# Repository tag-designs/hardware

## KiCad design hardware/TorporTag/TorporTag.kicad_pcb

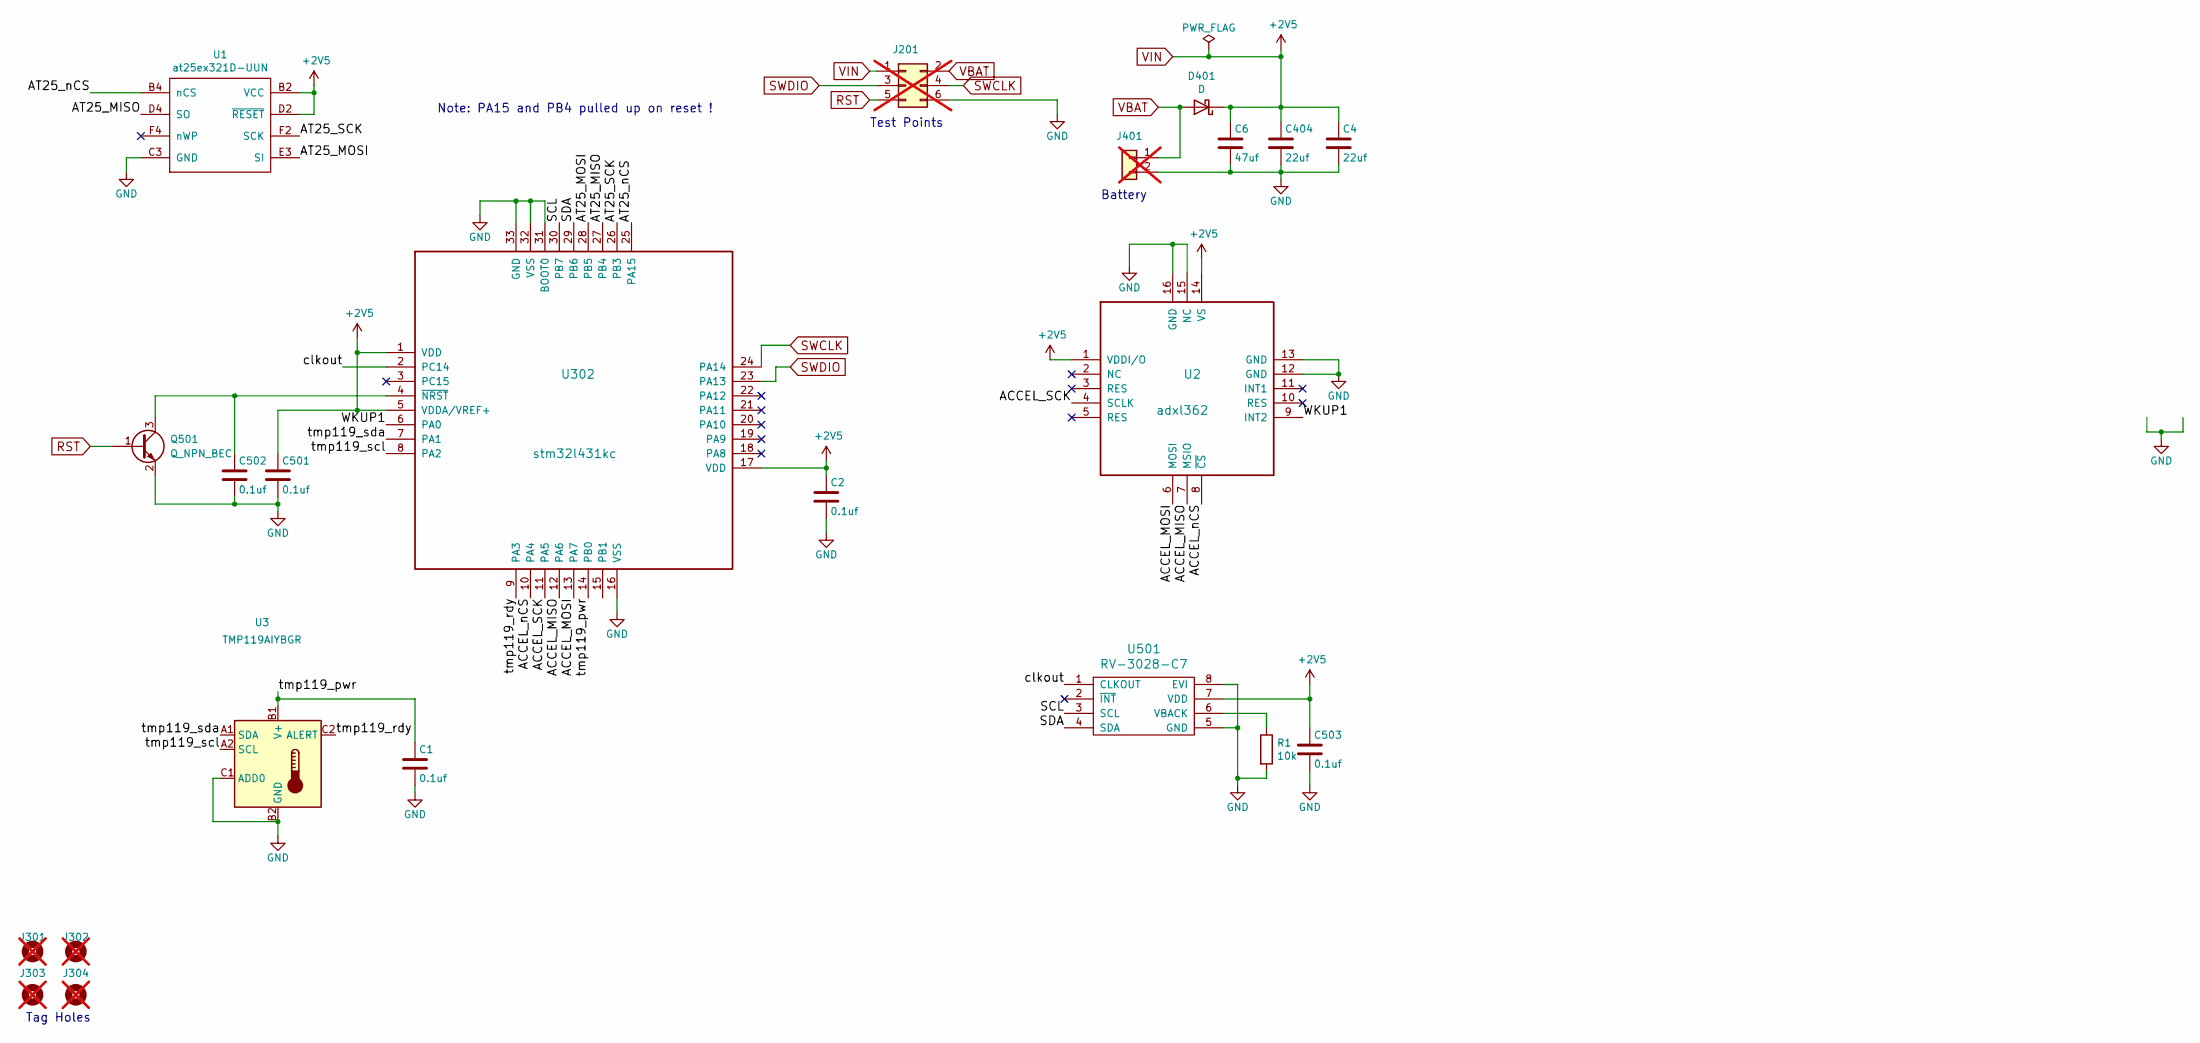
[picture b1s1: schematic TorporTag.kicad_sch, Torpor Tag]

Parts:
C1, C2, C501, C502, C503: 0.1uf; C_0201_0603Metric; MPN GRM033R60J104KE19D; LCSC C76928
C4, C404: 22uf; C_0402_1005Metric; MPN 04026D226MAT2A; LCSC C2179118
C6: 47uf; C_0603_1608Metric; MPN GRM188R60J476ME15D; LCSC C140782
D401: D; D_0402_1005Metric; MPN CDBQC0130L-HF; LCSC C2886012
J201: CONN_02X04; tagpoints6; not fitted
J301, J302, J303, J304: Conn_01x01; taghole1.1mm; not fitted
J401: CONN_01X02; MS621; not fitted
Q501: Q_NPN_BEC; SOT-883; MPN PMBT2222AMBYL; LCSC C552701
R1: 10k; R_0201_0603Metric; MPN RC0201FR-0710KL; LCSC C106225
U1: at25ex321D-UUN; adesto_wlcsp12; MPN AT25XE321D-UUN-T; LCSC C1858339
U2: adxl362; ADXL362; MPN ADXL362BCCZ-RL7; LCSC C192252
U3: TMP119AIYBGR; Texas_DSBGA-6_0.95x1.488mm_Layout2x3_P0.4mm; MPN TMP119AIYBGR; LCSC C22428347
U302: stm32l431kc; QFN-32-1EP_5x5mm_P0.5mm_EP3.45x3.45mm; MPN STM32L432KCU6; LCSC C1337280
U501: RV-3028-C7; RV-8803-C7; MPN RV-3028-C7 32.768KHZ 1PPM-TA-QA; LCSC C3019759

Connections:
/ACCEL_MISO: U2.7 (MSIO), U302.12 (PA6)
/ACCEL_MOSI: U2.6 (MOSI), U302.13 (PA7)
/ACCEL_SCK: U2.4 (SCLK), U302.11 (PA5)
/ACCEL_nCS: U2.8 (~CS), U302.10 (PA4)
/AT25_MISO: U1.D4 (SO), U302.27 (PB4)
/AT25_MOSI: U1.E3 (SI), U302.28 (PB5)
/AT25_SCK: U1.F2 (SCK), U302.26 (PB3)
/AT25_nCS: U1.B4 (nCS), U302.25 (PA15)
/SCL: U302.30 (PB7), U501.3 (SCL)
/SDA: U302.29 (PB6), U501.4 (SDA)
/WKUP1: U2.9 (INT2), U302.6 (PA0)
/clkout: U302.2 (PC14), U501.1 (CLKOUT)
/tmp119_pwr: C1.1, U3.B1 (V+), U302.14 (PB0)
/tmp119_rdy: U3.C2 (ALERT), U302.9 (PA3)
/tmp119_scl: U3.A2 (SCL), U302.8 (PA2)
/tmp119_sda: U3.A1 (SDA), U302.7 (PA1)
GND: C1.2, C2.2, C4.2, C6.2, C404.2, C501.2, C502.2, C503.2, J201.6, J401.2, Q501.2 (E), R1.2, U1.C3 (GND), U2.12 (GND), U2.13 (GND), U2.15 (NC), U2.16 (GND), U3.B2 (GND), U3.C1 (ADD0), U302.16 (VSS), U302.31 (BOOT0), U302.32 (VSS), U302.33 (GND), U501.5 (GND), U501.8 (EVI)
unnamed: C502.1, Q501.3 (C), U302.4 (~NRST)
unnamed: R1.1, U501.6 (VBACK)
RST: J201.5, Q501.1 (B)
SWCLK: J201.4, U302.24 (PA14)
SWDIO: J201.3, U302.23 (PA13)
VBAT: D401.2 (A), J201.2, J401.1
VIN: C2.1, C4.1, C6.1, C404.1, C501.1, C503.1, D401.1 (K), J201.1, U1.B2 (VCC), U1.D2 (~RESET), U2.1 (VDDI/O), U2.14 (VS), U302.1 (VDD), U302.5 (VDDA/VREF+), U302.17 (VDD), U501.7 (VDD)

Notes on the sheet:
Note: PA15 and PB4 pulled up on reset !
Tag Holes
Test Points
Battery

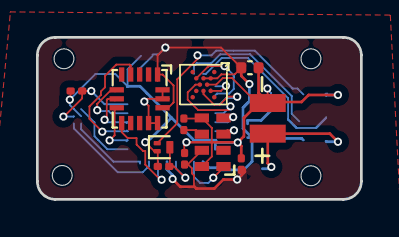
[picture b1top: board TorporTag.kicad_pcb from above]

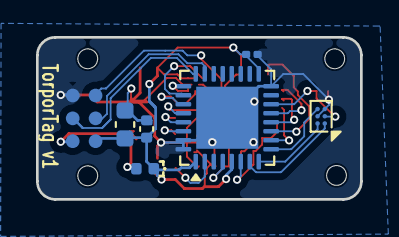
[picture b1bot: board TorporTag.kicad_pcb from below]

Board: 2 copper layers, 18.0 x 9.0 mm, 22 parts (7 on the bottom side), 24 nets.

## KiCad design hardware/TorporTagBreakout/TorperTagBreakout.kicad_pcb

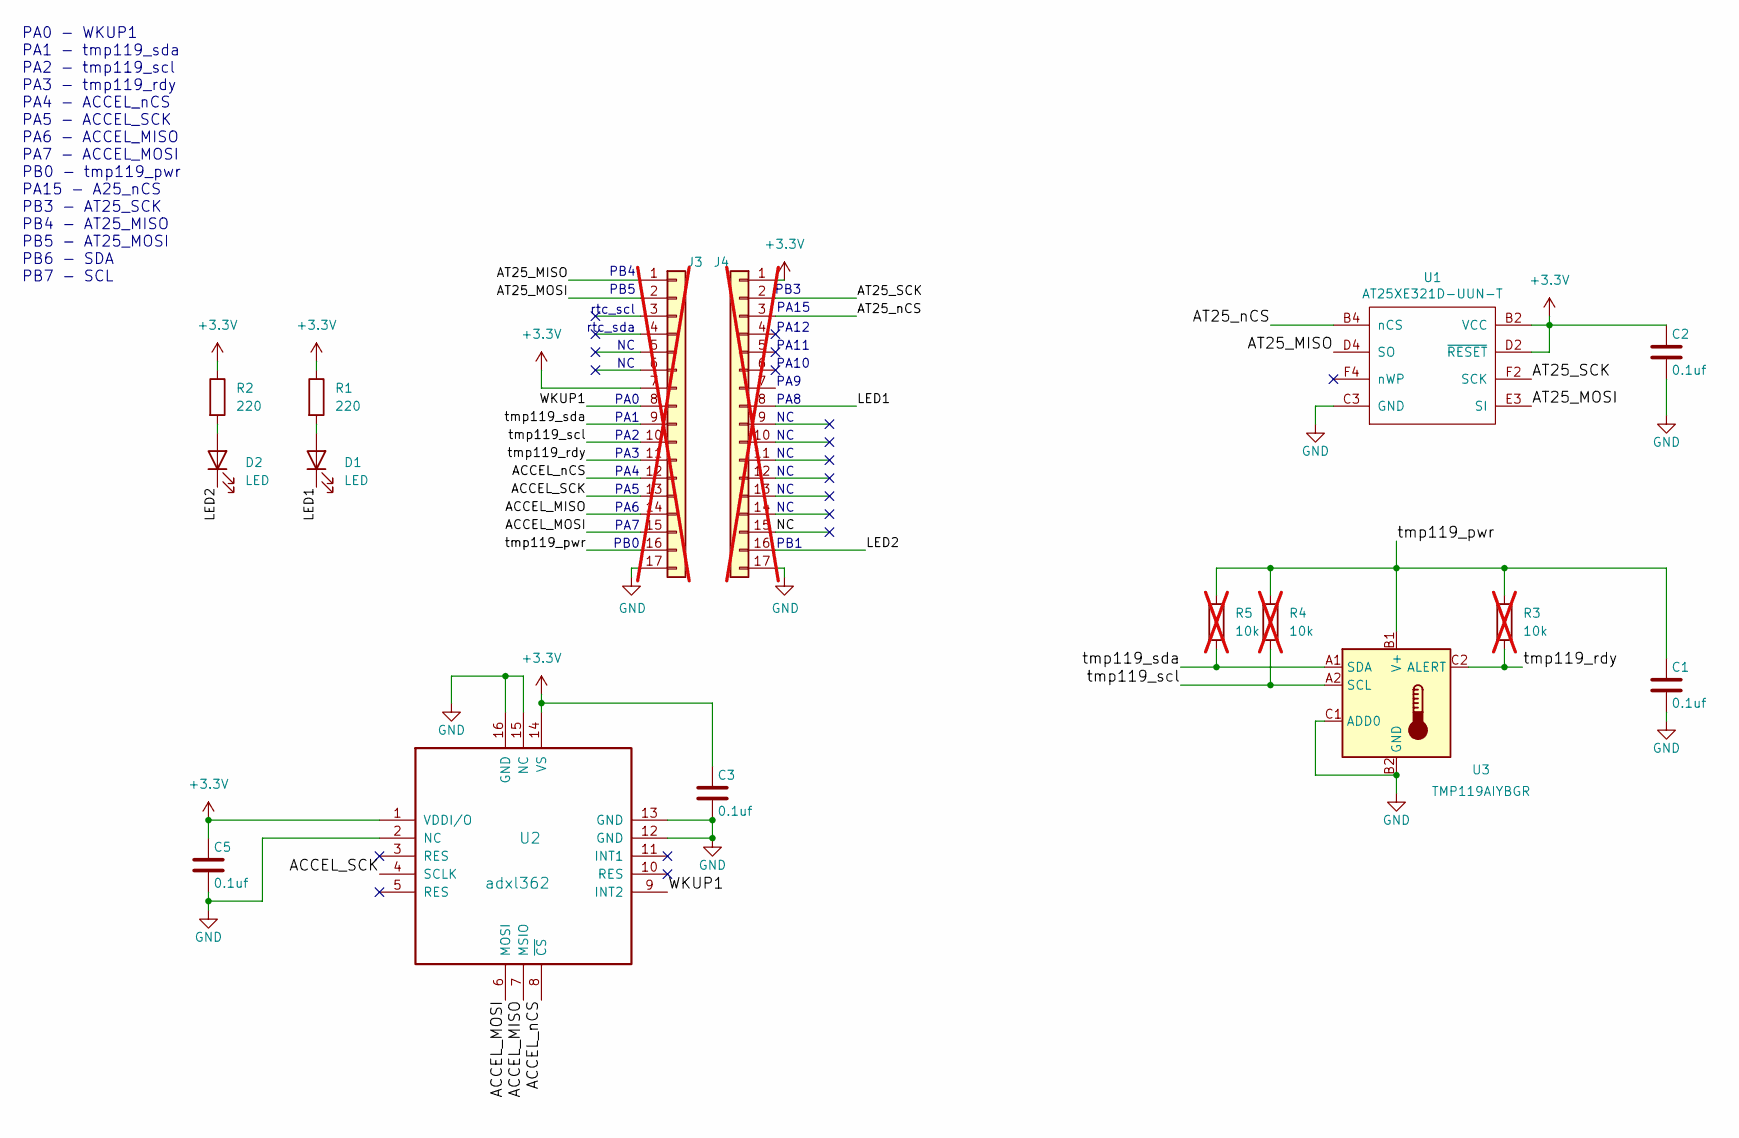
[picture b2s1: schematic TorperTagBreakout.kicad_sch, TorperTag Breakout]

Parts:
C1, C2, C3, C5: 0.1uf; C_0603_1608Metric; MPN CC0603KRX7R9BB104; LCSC C14663
D1, D2: LED; LED_0603_1608Metric; MPN KT-0603R; LCSC C2286
J3, J4: Conn_01x17; PinHeader_1x17_P2.54mm_Vertical_Staggered; not fitted
R1, R2: 220; R_0603_1608Metric; MPN 0603WAF2200T5E; LCSC C22962
R3, R4, R5: 10k; R_0805_2012Metric; MPN 0805W8F1002T5E; LCSC C17414; not fitted
U1: AT25XE321D-UUN-T; adesto_wlcsp12; MPN AT25XE321D-UUN-T; LCSC C1852767
U2: adxl362; ADXL362; MPN ADXL362BCCZ-RL; LCSC C59641
U3: TMP119AIYBGR; Texas_DSBGA-6_0.95x1.488mm_Layout2x3_P0.4mm; MPN TMP119AIYBGR; LCSC C22428347

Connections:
+3.3V: C2.1, C3.1, C5.1, J3.7, J4.1, R1.1, R2.1, U1.B2 (VCC), U1.D2 (~RESET), U2.1 (VDDI/O), U2.14 (VS)
/ACCEL_MISO: J3.14, U2.7 (MSIO)
/ACCEL_MOSI: J3.15, U2.6 (MOSI)
/ACCEL_SCK: J3.13, U2.4 (SCLK)
/ACCEL_nCS: J3.12, U2.8 (~CS)
/AT25_MISO: J3.1, U1.D4 (SO)
/AT25_MOSI: J3.2, U1.E3 (SI)
/AT25_SCK: J4.2, U1.F2 (SCK)
/AT25_nCS: J4.3, U1.B4 (nCS)
/LED1: D1.1 (K), J4.8
/LED2: D2.1 (K), J4.16
/NC: J4.15
/WKUP1: J3.8, U2.9 (INT2)
/tmp119_pwr: C1.1, J3.16, R3.1, R4.1, R5.1, U3.B1 (V+)
/tmp119_rdy: J3.11, R3.2, U3.C2 (ALERT)
/tmp119_scl: J3.10, R4.2, U3.A2 (SCL)
/tmp119_sda: J3.9, R5.2, U3.A1 (SDA)
GND: C1.2, C2.2, C3.2, C5.2, J3.17, J4.17, U1.C3 (GND), U2.2 (NC), U2.12 (GND), U2.13 (GND), U2.15 (NC), U2.16 (GND), U3.B2 (GND), U3.C1 (ADD0)
unnamed: D1.2 (A), R1.2
unnamed: D2.2 (A), R2.2

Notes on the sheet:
PA1
PA9
PA2
PA0
PA8
PA7
PA15
PA5
PA4
PB3
PA6
PA0 - WKUP1 PA1 - tmp119_sda PA2 - tmp119_scl PA3 - tmp119_rdy PA4 - ACCEL_nCS PA5 - ACCEL_SCK PA6 - ACCEL_MISO PA7 - ACCEL_MOSI PB0 - tmp119_pwr PA15 - A25_nCS PB3 - AT25_SCK PB4 - AT25_MISO PB5 - AT25_MOSI PB6 - SDA PB7 - SCL
PA3
PB4
PA12
PB0
PB5
PA10
rtc_sda
PA11
PB1
rtc_scl

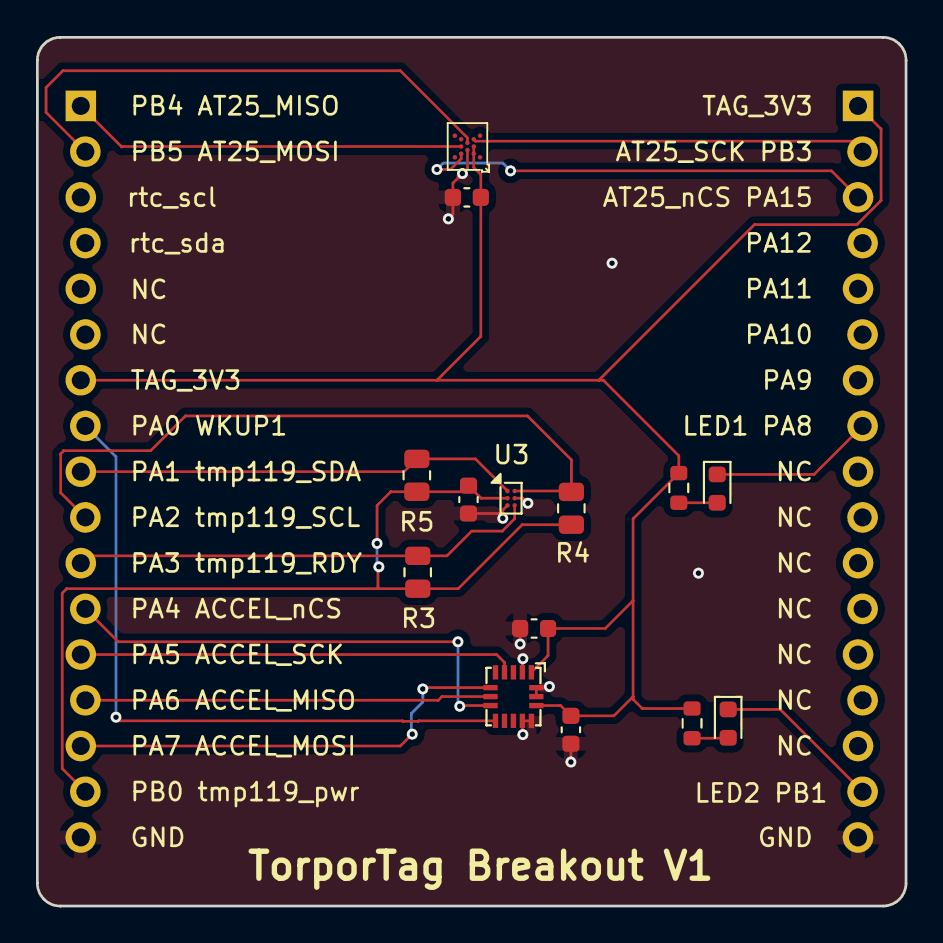
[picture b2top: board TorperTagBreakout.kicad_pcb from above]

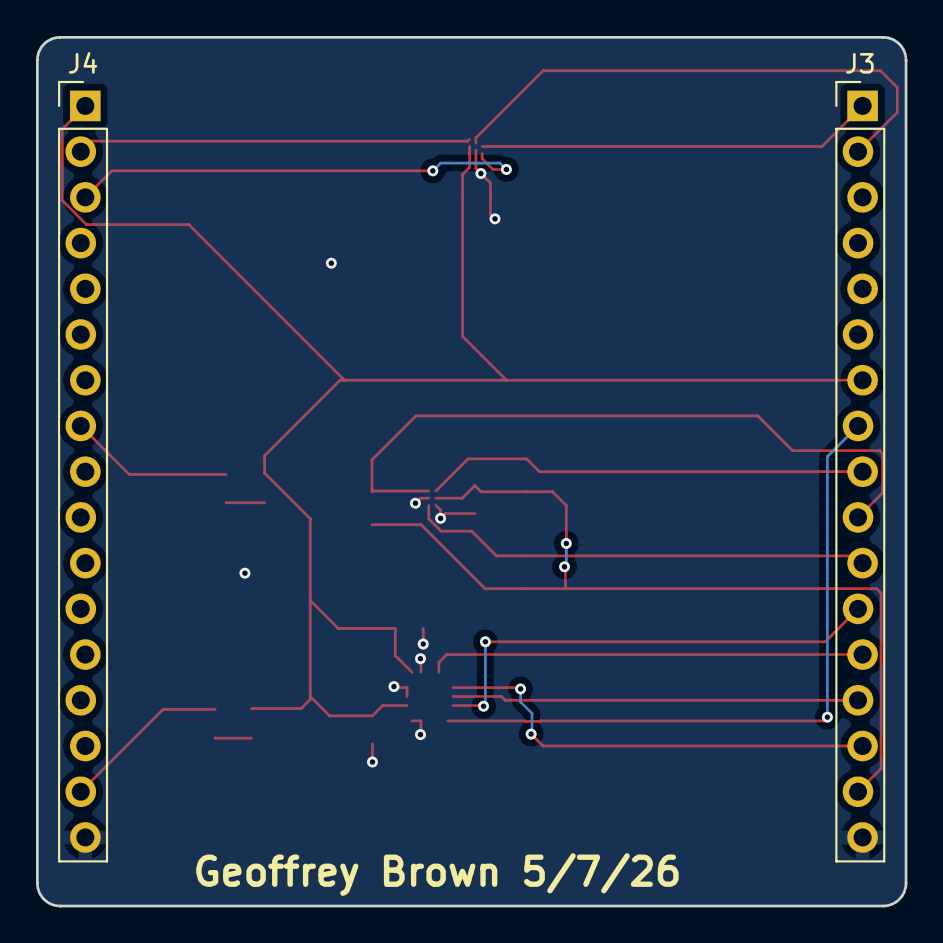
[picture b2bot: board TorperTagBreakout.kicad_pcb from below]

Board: 2 copper layers, 48.3 x 48.3 mm, 16 parts (2 on the bottom side), 19 nets.

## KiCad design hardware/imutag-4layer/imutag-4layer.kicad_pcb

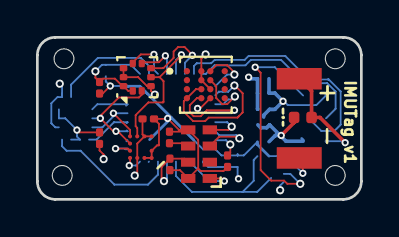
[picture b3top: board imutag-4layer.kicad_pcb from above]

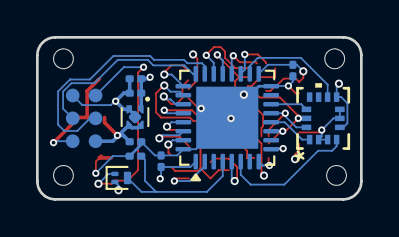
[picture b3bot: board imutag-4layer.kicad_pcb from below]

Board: 4 copper layers, 18.0 x 9.0 mm, 27 parts (11 on the bottom side), 29 nets.

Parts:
C1, C2, C3, C5, C9, C501, C502, C503: 0.1uf; C_0201_0603Metric
C4: 4.7uf; C_0201_0603Metric
C7, C8: 1uf; C_0201_0603Metric
D401: D; D_0402_1005Metric
J201: CONN_02X04; tagpoints6
J301, J302, J303, J304: Conn_01x01; taghole1.1mm
J401: CONN_01X02; batterypads
Q501: Q_NPN_BEC; SOT-883
R1: 10k; R_0201_0603Metric
U2: AK09940A; AK09940a
U3: LPS22DF; ST_HLGA-10_2x2mm_P0.5mm_LayoutBorder3x2y
U4: TPS7A2018PDQN; Texas_X2SON-4_1x1mm_P0.65mm
U5: LSM6DSV; LGA14-L_2P59X3P1X0P5_STM
U6: IC_MX25U12843GBBI00
U302: stm32l431kc; QFN-32-1EP_5x5mm_P0.5mm_EP3.45x3.45mm
U501: RV-3028-C7; RV-8803-C7

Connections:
+1V8: C1.1, C2.1, C3.1, C5.1, C8.1, C9.1, C501.1, C503.1, U2.B1 (VDD), U2.C4 (VOD), U2.D4 (RSTN), U3.1 (Vdd_IO), U3.10 (VDD), U4.1 (OUT), U5.5 (VDD_IO), U5.8 (VDD), U6.A2 (VCC), U6.B2 (~RESET), U6.C3 (~WP), U302.1 (VDD), U302.5 (VDDA/VREF+), U302.17 (VDD), U501.7 (VDD)
/AK_CS: U2.A2 (CSB), U302.9 (PA3)
/AK_TRG: U2.A1 (DRDY/TRG), U302.8 (PA2)
/AT25_MISO: U6.B3 (SO), U302.27 (PB4)
/AT25_MOSI: U6.D2 (SI), U302.28 (PB5)
/AT25_SCK: U6.C2 (SCLK), U6.D1, U302.26 (PB3)
/AT25_nCS: U6.A3 (~CS), U302.25 (PA15)
/LPS_CS: U3.6 (~CS), U302.20 (PA10)
/LPS_DRDY: U3.7 (INT_DRDY), U302.19 (PA9)
/LPS_MISO: U2.B4 (SO), U3.4 (SDA), U302.21 (PA11)
/LPS_MOSI: U3.5 (SA0), U302.22 (PA12)
/LSM_CK: U2.A3 (SCL/SK), U3.2 (SCL), U5.13 (SCL), U302.11 (PA5)
/LSM_CS: U5.12 (CS), U302.14 (PB0)
/LSM_MISO: U5.1 (SDO/SA0), U302.12 (PA6)
/LSM_MOSI: U2.A4 (SDA/SI), U5.14 (SDA), U302.13 (PA7)
/LSM_TRG: U5.9 (INT2), U302.18 (PA8)
/SCL: U302.30 (PB7), U501.3 (SCL)
/SDA: U302.29 (PB6), U501.4 (SDA)
/WKUP1: U5.4 (INT1), U302.6 (PA0)
/clkout: U302.2 (PC14), U501.1 (CLKOUT)
GND: C1.2, C2.2, C3.2, C4.1, C5.2, C7.2, C8.2, C9.2, C501.2, C502.2, C503.2, J201.6, J401.2, Q501.2 (E), R1.2, U2.C1 (VSS), U2.D1 (CAD0), U2.D2 (CAD1), U3.3 (GND), U3.8 (GND_IO), U3.9 (GND), U4.2 (GND), U4.5 (Pad), U5.2 (SDX), U5.3 (SCX), U5.6 (GND), U5.7 (GND), U6.D3 (GND), U302.16 (VSS), U302.32 (VSS), U302.33 (GND), U501.5 (GND), U501.8 (EVI)
unnamed: C502.1, Q501.3 (C), U302.4 (~NRST)
unnamed: C4.2, U302.31 (BOOT0)
unnamed: R1.1, U501.6 (VBACK)
RST: J201.5, Q501.1 (B)
SWCLK: J201.4, U302.24 (PA14)
SWDIO: J201.3, U302.23 (PA13)
VBAT: D401.2 (A), J201.2, J401.1
VIN: C7.1, D401.1 (K), J201.1, U4.3 (EN), U4.4 (IN)

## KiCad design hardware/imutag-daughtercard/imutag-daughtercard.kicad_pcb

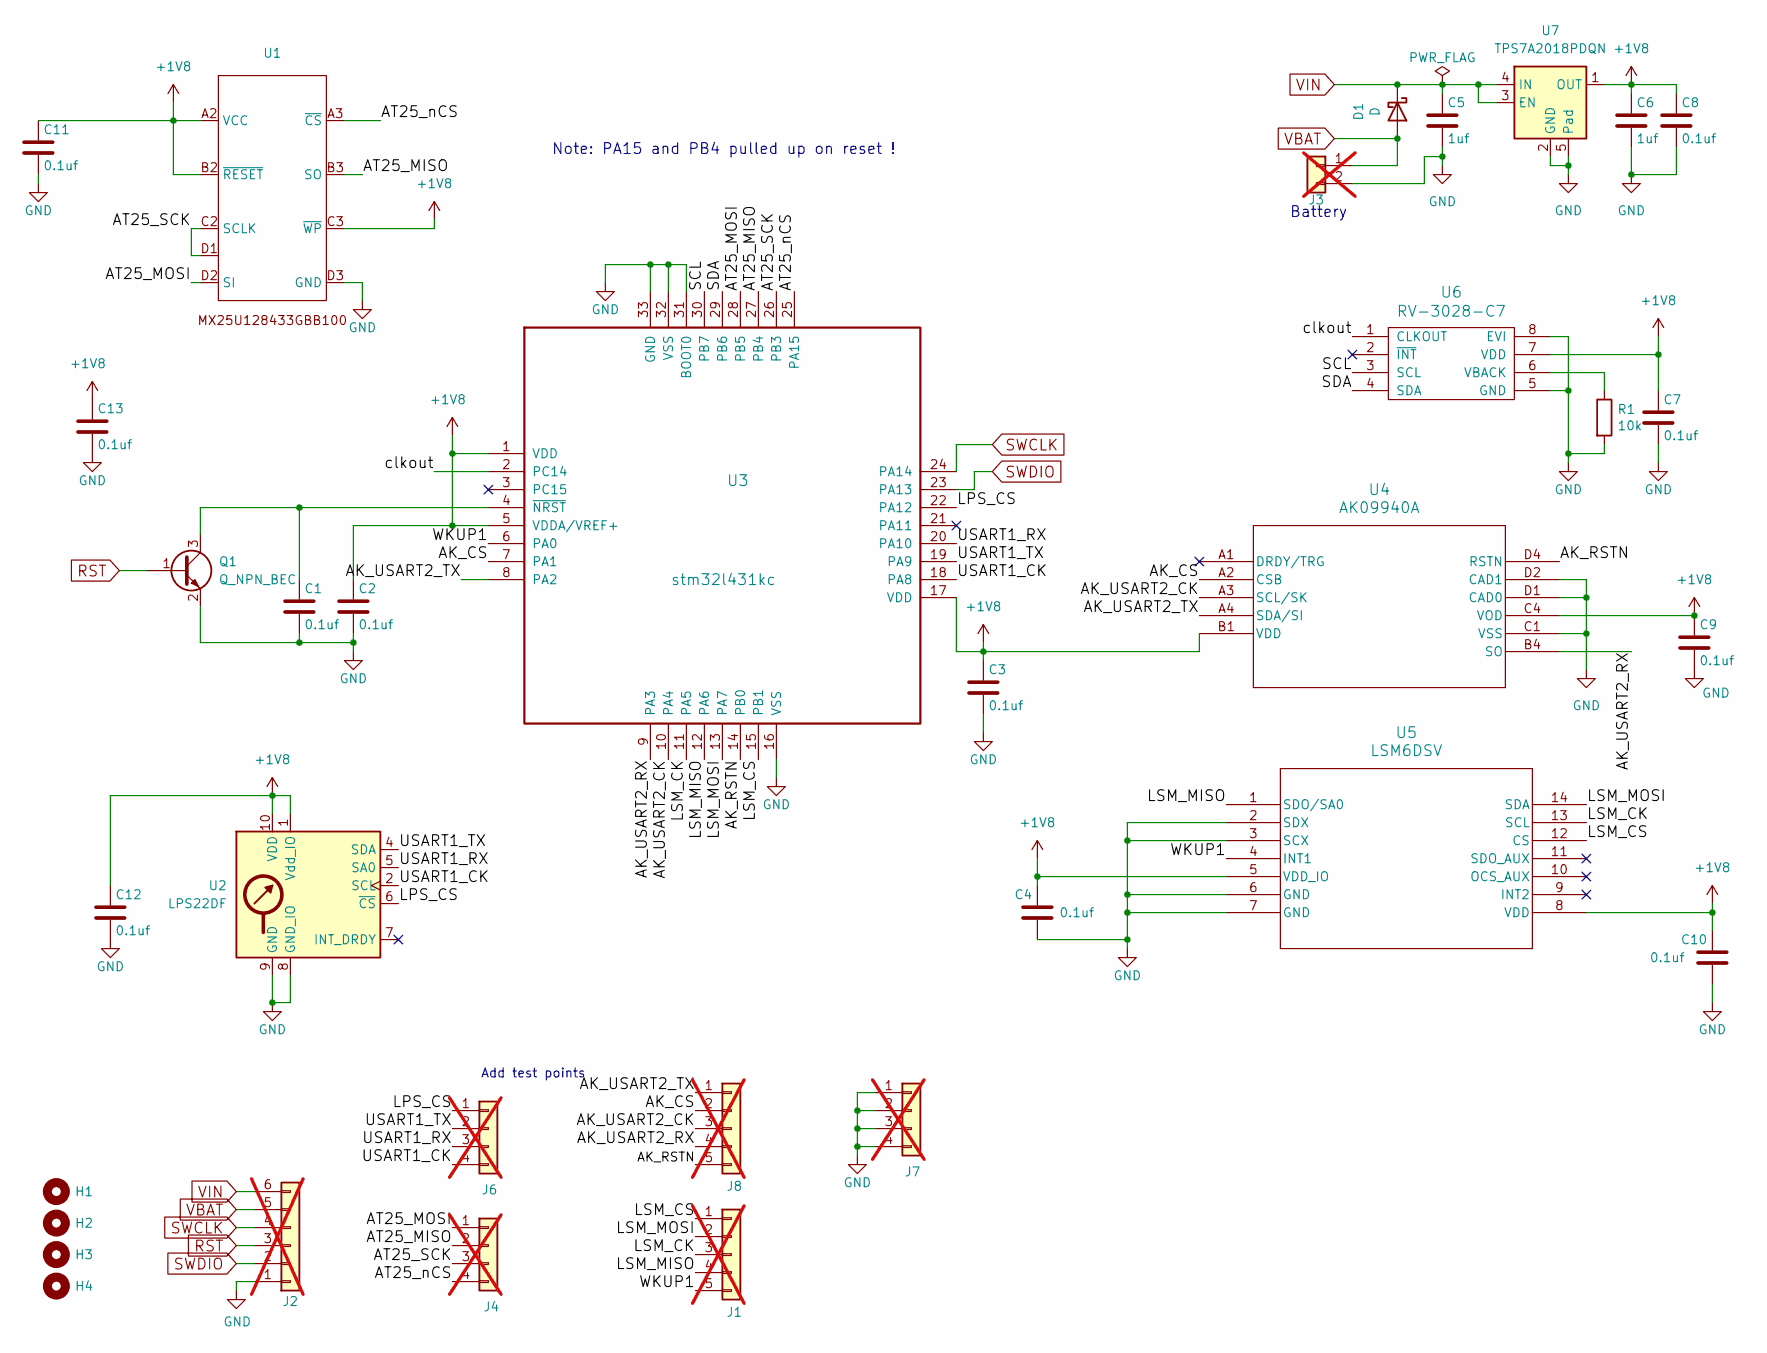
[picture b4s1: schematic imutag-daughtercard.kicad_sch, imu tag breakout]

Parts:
C1, C2, C4, C7, C10, C11, C12, C13: 0.1uf; C_0201_0603Metric; MPN C181047; LCSC C181047
C3: 0.1uf; C_0201_0603Metric; MPN GRM033R60J105MEA2D; LCSC C76929
C5, C6: 1uf; C_0201_0603Metric; MPN GRM033R60J105MEA2D
C8, C9: 0.1uf; C_0201_0603Metric; MPN GRM033C81E104KE14D
D1: D; D_0402_1005Metric; MPN CDBQC0130L-HF; LCSC C2886012
H1, H2, H3, H4: MountingHole; MountingHole_2.5mm
J1, J8: Conn_01x05; PinHeader_1x05_P2.54mm_Vertical; not fitted
J2: Conn_01x06; JST_B6B-ZR_LF__SN_; not fitted
J3: CONN_01X02; batterypads; not fitted
J4, J6, J7: Conn_01x04; PinHeader_1x04_P2.54mm_Vertical; not fitted
Q1: Q_NPN_BEC; SOT-883; MPN BC847AMB,315; LCSC C686658
R1: 10k; R_0201_0603Metric; MPN RC0201FR-0710KL; LCSC C106225
U1: IC_MX25U12843GBBI00; MPN MX25U12843GBBI00; LCSC C7316586
U2: LPS22DF; ST_HLGA-10_2x2mm_P0.5mm_LayoutBorder3x2y
U3: stm32l431kc; QFN-32-1EP_5x5mm_P0.5mm_EP3.45x3.45mm; MPN STM32L432KCU6; LCSC C1337280
U4: AK09940A; AK09940a; MPN AK09940A
U5: LSM6DSV; LGA14-L_2P59X3P1X0P5_STM
U6: RV-3028-C7; RV-8803-C7; MPN RV-3028-C7 32.768KHZ 1PPM-TA-QA; LCSC C3019759
U7: TPS7A2018PDQN; Texas_X2SON-4_1x1mm_P0.65mm; MPN TPS7A2018PDQNR

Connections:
+1V8: C2.1, C3.1, C4.1, C6.1, C7.1, C8.1, C9.1, C10.1, C11.1, C12.1, C13.1, U1.A2 (VCC), U1.B2 (~RESET), U1.C3 (~WP), U2.1 (Vdd_IO), U2.10 (VDD), U3.1 (VDD), U3.5 (VDDA/VREF+), U3.17 (VDD), U4.B1 (VDD), U4.C4 (VOD), U5.5 (VDD_IO), U5.8 (VDD), U6.7 (VDD), U7.1 (OUT)
/AK_CS: J8.2, U3.7 (PA1), U4.A2 (CSB)
/AK_RSTN: J8.5, U3.14 (PB0), U4.D4 (RSTN)
/AK_USART2_CK: J8.3, U3.10 (PA4), U4.A3 (SCL/SK)
/AK_USART2_RX: J8.4, U3.9 (PA3), U4.B4 (SO)
/AK_USART2_TX: J8.1, U3.8 (PA2), U4.A4 (SDA/SI)
/AT25_MISO: J4.2, U1.B3 (SO), U3.27 (PB4)
/AT25_MOSI: J4.1, U1.D2 (SI), U3.28 (PB5)
/AT25_SCK: J4.3, U1.C2 (SCLK), U1.D1, U3.26 (PB3)
/AT25_nCS: J4.4, U1.A3 (~CS), U3.25 (PA15)
/LPS_CS: J6.1, U2.6 (~CS), U3.22 (PA12)
/LSM_CK: J1.3, U3.11 (PA5), U5.13 (SCL)
/LSM_CS: J1.1, U3.15 (PB1), U5.12 (CS)
/LSM_MISO: J1.4, U3.12 (PA6), U5.1 (SDO/SA0)
/LSM_MOSI: J1.2, U3.13 (PA7), U5.14 (SDA)
/SCL: U3.30 (PB7), U6.3 (SCL)
/SDA: U3.29 (PB6), U6.4 (SDA)
/USART1_CK: J6.4, U2.2 (SCL), U3.18 (PA8)
/USART1_RX: J6.3, U2.5 (SA0), U3.20 (PA10)
/USART1_TX: J6.2, U2.4 (SDA), U3.19 (PA9)
/WKUP1: J1.5, U3.6 (PA0), U5.4 (INT1)
/clkout: U3.2 (PC14), U6.1 (CLKOUT)
GND: C1.2, C2.2, C3.2, C4.2, C5.2, C6.2, C7.2, C8.2, C9.2, C10.2, C11.2, C12.2, C13.2, J2.1, J3.2, J7.1, J7.2, J7.3, J7.4, Q1.2 (E), R1.2, U1.D3 (GND), U2.3 (GND), U2.8 (GND_IO), U2.9 (GND), U3.16 (VSS), U3.31 (BOOT0), U3.32 (VSS), U3.33 (GND), U4.C1 (VSS), U4.D1 (CAD0), U4.D2 (CAD1), U5.2 (SDX), U5.3 (SCX), U5.6 (GND), U5.7 (GND), U6.5 (GND), U6.8 (EVI), U7.2 (GND), U7.5 (Pad)
unnamed: C1.1, Q1.3 (C), U3.4 (~NRST)
unnamed: R1.1, U6.6 (VBACK)
RST: J2.3, Q1.1 (B)
SWCLK: J2.4, U3.24 (PA14)
SWDIO: J2.2, U3.23 (PA13)
VBAT: D1.2 (A), J2.5, J3.1
VIN: C5.1, D1.1 (K), J2.6, U7.3 (EN), U7.4 (IN)

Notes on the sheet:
Battery
Add test points
Note: PA15 and PB4 pulled up on reset !

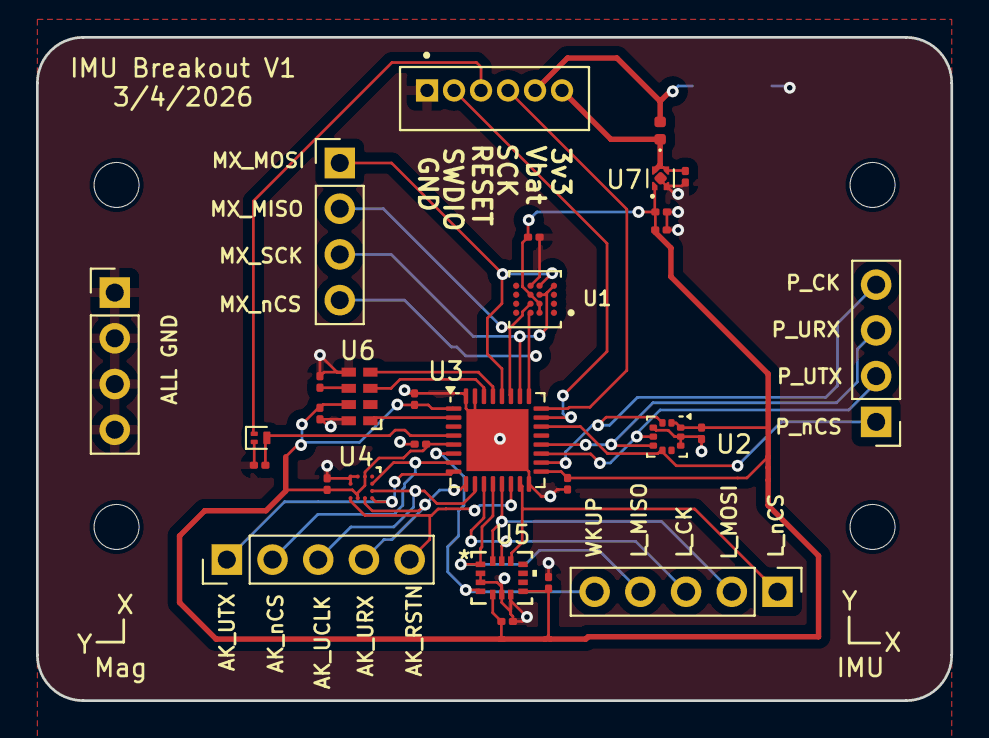
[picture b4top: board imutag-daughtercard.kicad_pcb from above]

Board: 2 copper layers, 50.8 x 36.9 mm, 34 parts (1 on the bottom side), 30 nets.

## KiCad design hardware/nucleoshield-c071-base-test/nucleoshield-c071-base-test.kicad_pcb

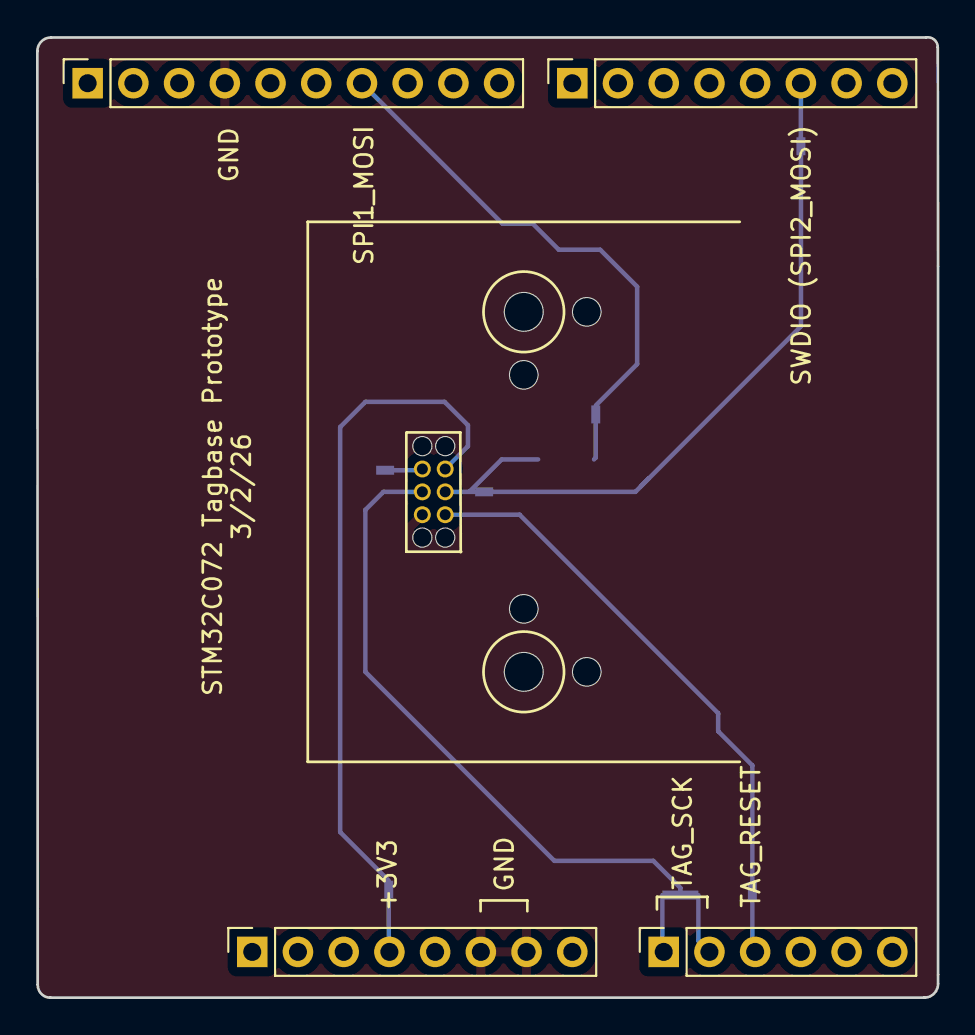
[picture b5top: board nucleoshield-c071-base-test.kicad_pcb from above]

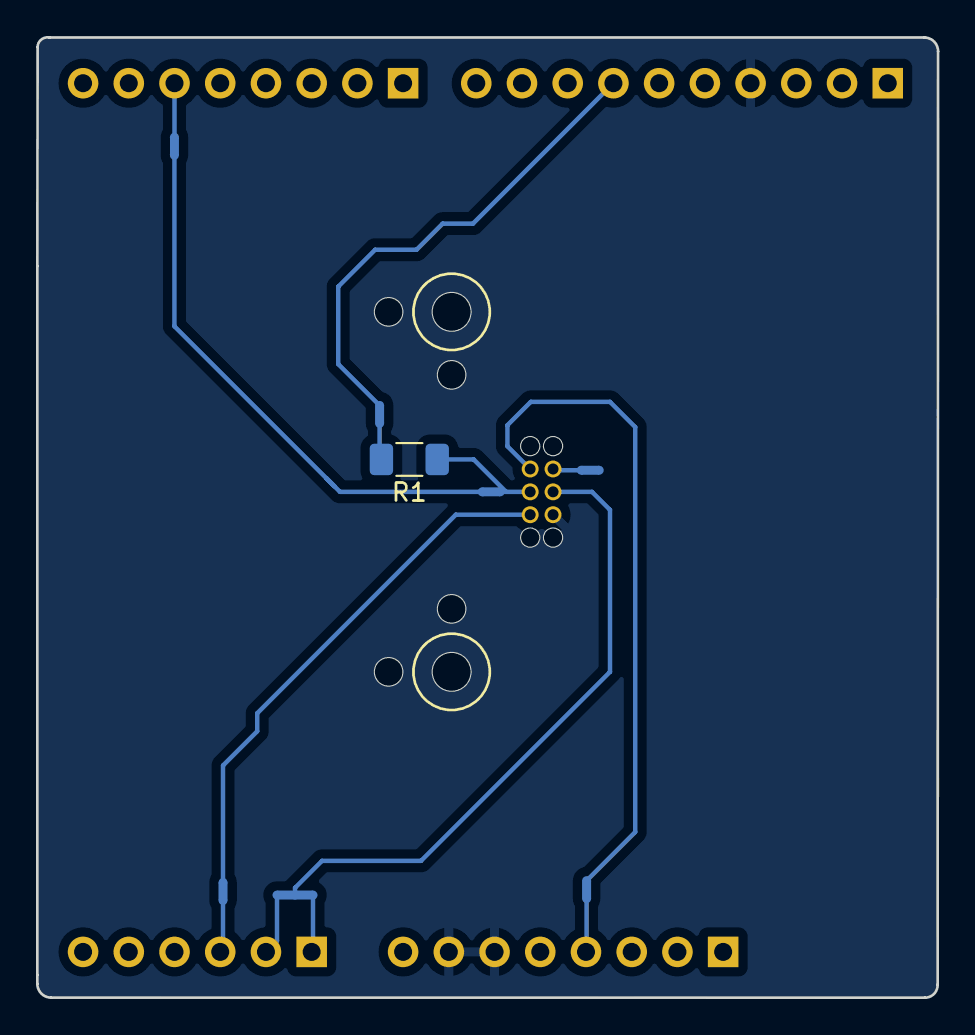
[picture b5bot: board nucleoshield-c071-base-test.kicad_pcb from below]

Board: 2 copper layers, 50.0 x 53.4 mm, 13 parts (8 on the bottom side), 14 nets.

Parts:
J1: Power; PinSocket_1x08_P2.54mm_Vertical
J2: Digital/PWM; PinSocket_1x10_P2.54mm_Vertical
J3: Analog; PinSocket_1x06_P2.54mm_Vertical
J4: Digital/PWM; PinSocket_1x08_P2.54mm_Vertical
J5: Conn_02x03_Odd_Even; 6pin_tagpoints_new_offset
NT1, NT3, NT4, NT5, NT6, NT7: NetTie_2; NetTie-2_SMD_Pad0.5mm
NT2: NetTie_3; NetTie-3_SMD_Pad0.5mm
R1: 1K; R_1206_3216Metric_Pad1.30x1.75mm_HandSolder

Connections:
+3V3: J1.4, NT7.1
/PA0: J3.1, NT2.1
/PA1: J3.2, NT2.3
/PA4: J3.3, NT6.1
/PA7: J2.7, NT3.1
/PA10: J4.6, NT4.1
/SPI1_MOSI: NT3.2, R1.2
/SPI2_MOSI: NT1.1, NT4.2
GND: J1.6, J1.7, J2.4, J5.2
TAG_3V3: J5.5, NT7.2
TAG_RESET: J5.1, NT6.2
TAG_SCK: J5.4, NT2.2
TAG_SWDIO: J5.3, NT1.2, R1.1
TAG_VBAT: J5.6, NT5.2

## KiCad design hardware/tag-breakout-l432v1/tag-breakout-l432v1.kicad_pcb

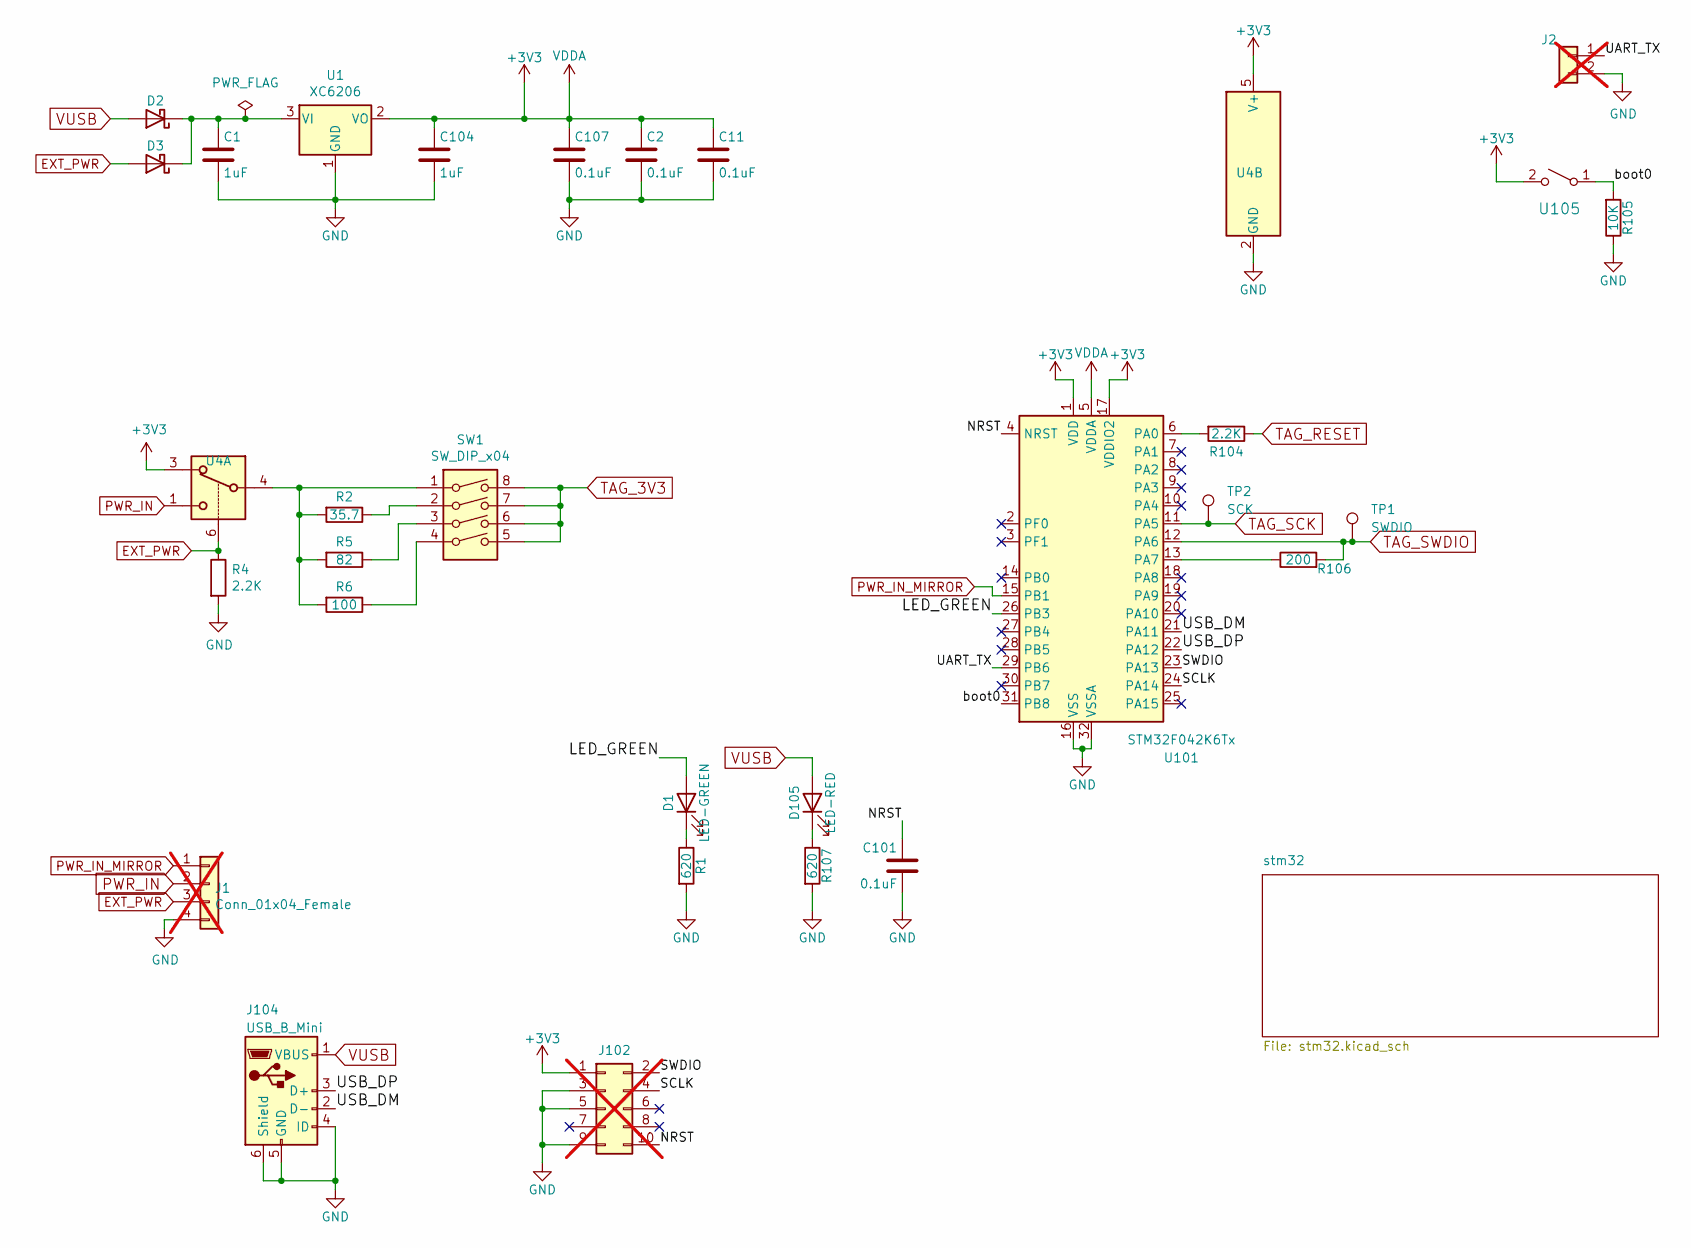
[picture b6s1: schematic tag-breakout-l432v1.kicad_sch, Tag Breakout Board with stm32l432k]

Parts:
C1, C104: 1uF; C_0603_1608Metric; MPN CL10A105KB8NNNC; LCSC C15849
C2, C11, C101, C107: 0.1uF; C_0603_1608Metric; MPN CC0603KRX7R9BB104; LCSC C14663
D1: LED-GREEN; LED_0603_1608Metric; MPN 19-217/GHC-YR1S2/3T; LCSC C72043
D2, D3: D_Schottky; D_SOD-123; LCSC C8598
D105: LED-RED; LED_0603_1608Metric; MPN KT 0603R; LCSC C2286
J1: Conn_01x04_Female; JST_XH_B04B-XH-AM_1x04_P2.50mm_Vertical; not fitted
J2: Conn_01x02_Male; PinHeader_1x02_P2.54mm_Vertical; not fitted
J102: Conn_02x05_Odd_Even; FTSH-105-01-F-D-K; not fitted
J104: USB_B_Mini; USB_Mini-B_Lumberg_2486_01_Horizontal; MPN MINI 5PTP; LCSC C2681563
R1, R107: 620; R_0603_1608Metric; MPN 0603WAF6200T5E; LCSC C23220
R2: 35.7; R_0603_1608Metric; LCSC C158925
R4, R104: 2.2K; R_0603_1608Metric; MPN 0603WAF1002T5E; LCSC C4190
R5: 82; R_0603_1608Metric; LCSC C23255
R6: 100; R_0603_1608Metric; MPN 0603WAF1000T5E; LCSC C22775
R105: 10K; R_0603_1608Metric; MPN 0603WAF1002T5E; LCSC C25804
R106: 200; R_0603_1608Metric; MPN 0603WAF1000T5E; LCSC C8218
SW1: SW_DIP_x04; SW_DIP_SPSTx04_Slide_KingTek_DSHP04TS_W7.62mm_P1.27mm; MPN DSHP04TSGET; LCSC C40736
TP1: SWDIO; TestPoint_Pad_D2.0mm
TP2: SCK; TestPoint_Pad_D2.0mm
U1: XC6206; SOT-23-3; MPN XC6206P332MR; LCSC C5446
U4: TS5A3159ADBVR; SOT-23-6; MPN TS5A3159ADBVR; LCSC C128405
U101: STM32F042K6Tx; LQFP-32_7x7mm_P0.8mm; LCSC C69216
U105: Tactile Switch; SW_SPST_TS_1187; MPN TS-1187A-C-E-B; LCSC C318889

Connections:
+3V3: C2.1, C11.1, C104.1, C107.1, J102.1, U1.2 (VO), U4.3, U4.5 (V+), U101.1 (VDD), U101.5 (VDDA), U101.17 (VDDIO2), U105.2 (B)
/LED_GREEN: D1.2 (A), U101.26 (PB3)
/NRST: C101.1, J102.10, U101.4 (NRST)
/SCLK: J102.4, U101.24 (PA14)
/SWDIO: J102.2, U101.23 (PA13)
/UART_TX: J2.1, U101.29 (PB6)
/USB_DM: J104.2 (D-), U101.21 (PA11)
/USB_DP: J104.3 (D+), U101.22 (PA12)
/boot0: R105.2, U101.31 (PB8), U105.1 (A)
EXT_PWR: D3.2 (A), J1.3, R4.1, U4.6
GND: C1.2, C2.2, C11.2, C101.2, C104.2, C107.2, J1.4, J2.2, J102.3, J102.5, J102.9, J104.4 (ID), J104.5 (GND), J104.6 (Shield), R1.2, R4.2, R105.1, R107.2, U1.1 (GND), U4.2 (GND), U101.16 (VSS), U101.32 (VSSA); also elsewhere on the board
unnamed: D1.1 (K), R1.1
unnamed: C1.1, D2.1 (K), D3.1 (K), U1.3 (VI)
unnamed: D105.1 (K), R107.1
unnamed: R2.1, SW1.2
unnamed: R2.2, R5.2, R6.2, SW1.1, U4.4
unnamed: R5.1, SW1.3
unnamed: R6.1, SW1.4
unnamed: R104.2, U101.6 (PA0)
unnamed: R106.1, U101.13 (PA7)
PWR_IN: J1.2, U4.1
PWR_IN_MIRROR: J1.1, U101.15 (PB1)
TAG_3V3: SW1.5, SW1.6, SW1.7, SW1.8; also elsewhere on the board
TAG_RESET: R104.1; also elsewhere on the board
TAG_SCK: TP2.1, U101.11 (PA5); also elsewhere on the board
TAG_SWDIO: R106.2, TP1.1, U101.12 (PA6); also elsewhere on the board
VUSB: D2.2 (A), D105.2 (A), J104.1 (VBUS)
